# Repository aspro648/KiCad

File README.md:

# KiCad
My design files. Abandon all hope ye who enter here.

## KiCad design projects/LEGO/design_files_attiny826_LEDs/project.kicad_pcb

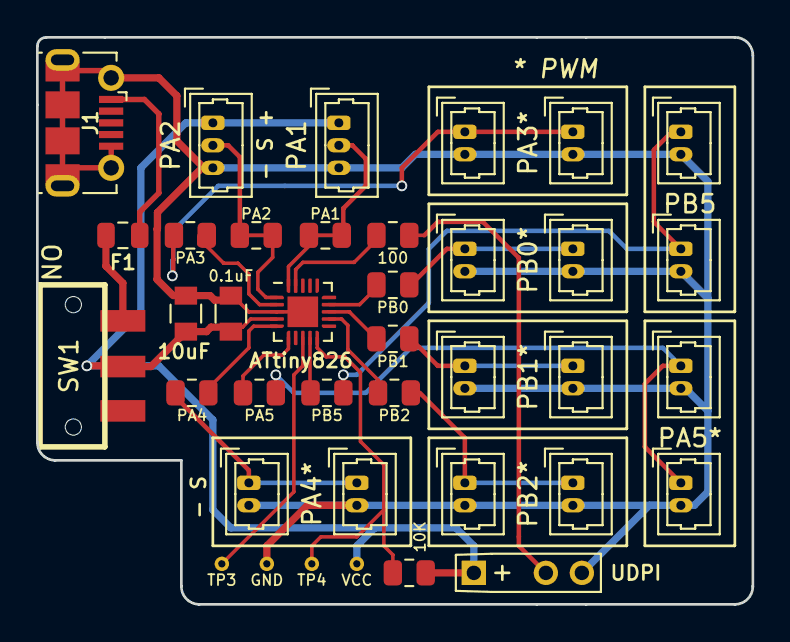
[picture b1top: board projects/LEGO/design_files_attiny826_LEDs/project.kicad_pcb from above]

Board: 2 copper layers, 39.8 x 31.5 mm, 38 parts (0 on the bottom side), 24 nets.

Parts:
C1: 10uF; C_0805
C2: 0.1uF; C_0805
F1: Polyfuse; Fuse_0805_2012Metric
J1: USB-MICRO; USB_Micro-B_Molex-105017-0001
J2, J10: PA4*; Molex_PicoBlade_53047-0210_1x02_P1.25mm_Vertical
J3: UDPI; UDPI_header
J4, J11: PA5*; Molex_PicoBlade_53047-0210_1x02_P1.25mm_Vertical
J5, J12: PB2*; Molex_PicoBlade_53047-0210_1x02_P1.25mm_Vertical
J6, J13: PB0*; Molex_PicoBlade_53047-0210_1x02_P1.25mm_Vertical
J7, J15: PB1*; Molex_PicoBlade_53047-0210_1x02_P1.25mm_Vertical
J8, J16: PA3*; Molex_PicoBlade_53047-0210_1x02_P1.25mm_Vertical
J9: PA2; Molex_PicoBlade_53047-0310_1x03_P1.25mm_Vertical
J14: PA1; Molex_PicoBlade_53047-0310_1x03_P1.25mm_Vertical
J17, J18: PB5; Molex_PicoBlade_53047-0210_1x02_P1.25mm_Vertical
JP1: PA2; J_0805
JP2: PA1; J_0805
R1: PA5; R_0805_2012Metric
R2: PB2; R_0805_2012Metric
R3: 100; R_0805_2012Metric
R4: PB0; R_0805_2012Metric
R5: PB1; R_0805_2012Metric
R6: PA4; R_0805_2012Metric
R7: PA3; R_0805_2012Metric
R8: PB5; R_0805_2012Metric
R9: 10K; R_0805_2012Metric
SW1: SW_SPST; SPST_SMD
TP1: GND; TestPoint
TP2: VCC; TestPoint
TP3: PA7; TestPoint
TP4: PB4; TestPoint
U1: ATtiny826; VQFN-20-1EP_3x3mm_P0.4mm_EP1.7x1.7mm

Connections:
/PIN_PA1: J14.2, JP2.1, JP2.2, U1.20
/PIN_PA2: J9.2, JP1.1, JP1.2, U1.1
/PIN_PA3: R7.1, U1.2
/PIN_PA4: R6.1, U1.5
/PIN_PA5: R1.1, U1.6
/PIN_PA7: TP3.1, U1.8
/PIN_PB0: R4.1, U1.14
/PIN_PB1: R5.1, U1.13
/PIN_PB2: R2.1, U1.12
/PIN_PB4: R9.2, TP4.1, U1.10
/PIN_PB5: R8.1, U1.9
/UPDI: R3.1, U1.19
GND: C1.2, C2.2, J1.5, J1.6, J2.2, J3.4, J4.2, J5.2, J6.2, J7.2, J8.2, J9.3, J10.2, J11.2, J12.2, J13.2, J14.3, J15.2, J16.2, J17.2, J18.2, TP1.1, U1.3, U1.21
unnamed: F1.2, J1.1
unnamed: J3.3, R3.2
unnamed: J2.1, J10.1, R6.2
unnamed: J4.1, J11.1, R1.2
unnamed: J5.1, J12.1, R2.2
unnamed: J6.1, J13.1, R4.2
unnamed: J7.1, J15.1, R5.2
unnamed: J8.1, J16.1, R7.2
unnamed: J17.1, J18.1, R8.2
VBUS: F1.1, SW1.1
VCC: C1.1, C2.1, J3.1, J9.1, J14.1, R9.1, SW1.2, TP2.1, U1.4

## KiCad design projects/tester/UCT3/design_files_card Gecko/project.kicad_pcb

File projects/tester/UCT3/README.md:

Universal Cable Tester V3

Bill Of Materials
----------------
  
- 1 ea., Perfect Purple PCB from OSH Park, with not so perfect layout from kicad.pcb file.
- 1 ea., U4 ATMEGA32U4-AU, IC MCU 8BIT 32KB FLASH 44TQFP, https://www.digikey.com/short/jb25pc
- 1 ea., Y1 CER RES 16.0000MHZ 15PF SMD, Murata CSTNE16M0V530000R0, https://www.digikey.com/short/8nzcmjh3
- 2 ea., C1 CAP CER 10UF 10V X5R 0805, Kemet C0805C106K8PAC7800, https://www.digikey.com/short/32v75tfv
- 23 ea., D1-D23 SMD LED GREEN 0603, Lite-On LTST-C191KGKT, https://www.digikey.com/short/ptwhtwz2
- 1 ea., F1 PTC RESET FUSE 6V 350MA 0805, Bell 0ZCK0035FF2G, https://www.digikey.com/short/b0qhczzp
- 2 ea., RV1, RV2 VARISTOR 10.8V 30A 0603, KYOCERA VCUG060050L1DP, https://www.digikey.com/short/0479hw0m
- 23 ea., R1-R23 Resistor 1K OHM SMD 0603, Stackpole RNCP0603FTD1K00, https://www.digikey.com/short/704h9hfn
- 2 ea., R24, R25 Resistor 22 OHM SMD 0603, Yageo RC0603JR-0722RL, https://www.digikey.com/short/93jrm3t2
- 1 ea., R26 Resistor 1M OHM SMD 0603 Yageo RC0603JR-071ML, https://www.digikey.com/short/z0jnrwbq
- 2 ea., SW1 SWITCH TACTILE SPST-NO 0.05A 12V, Wurth 434121025816, https://www.digikey.com/short/qbm0p0c9
- 1 ea., J1 CONN RCPT MICRO USB R/A SMD, Molex 1050170001, https://www.digikey.com/short/jb2205
- 2 ea., X1, X2 CONN EDGE DUAL FMALE 20POS, Samtek MEC8-110-02-L-D-RA1, https://www.digikey.com/short/f4rv8cjm
- 2 ea., ROUND STANDOFF M2.5 STEEL 2.7MM, Wurth 9774027151R, https://www.digikey.com/short/47zwt3m4
- 2 ea., M2.5x6 pan-head phillips screw
- 2 ea., Resistor 4K7 OHM SMD 0603

- 1 ea., 3535 RGB LED,  IN-PI33TBTPRPGPB https://www.digikey.com/short/qf2t8bqj

Card:
10K
24LC32AT-I/MC, https://www.digikey.com/short/r3f225vm
- 2 ea., M2.5 thumbscrew https://www.mcmaster.com/99607A263/
https://www.amazon.com/M2-5x6mm-Knurled-Screws-Stainless-Metric/dp/B01NBH813V

License
----------------
[Attribution-ShareAlike 3.0 United States (CC BY-SA 3.0 US)](https://creativecommons.org/licenses/by-sa/3.0/us/)

You are free to:

- Share — copy and redistribute the material in any medium or format
- Adapt — remix, transform, and build upon the material

Under the following terms:

- Attribution — You must give appropriate credit, provide a link to the license, and indicate if changes were made. You may do so in any reasonable manner, but not in any way that suggests the licensor endorses you or your use.
- ShareAlike — If you remix, transform, or build upon the material, you must distribute your contributions under the same license as the original.

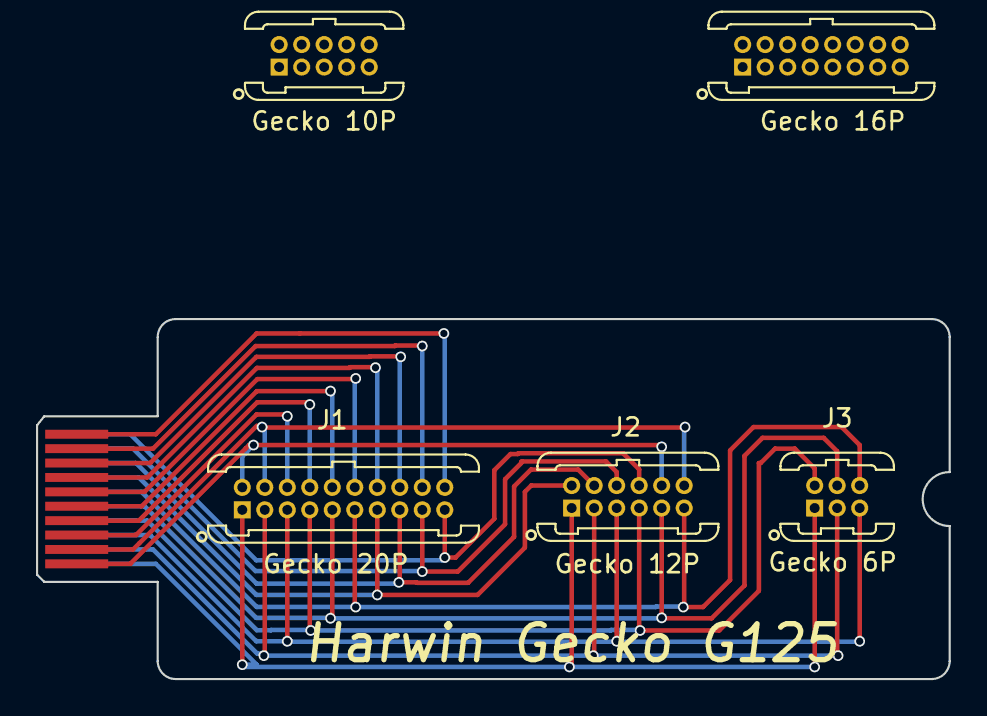
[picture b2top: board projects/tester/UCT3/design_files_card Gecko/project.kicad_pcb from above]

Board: 2 copper layers, 50.7 x 20.0 mm, 4 parts (0 on the bottom side), 20 nets.

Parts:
J0: Edge; MEC8_card
J1: Gecko 20P; Harwin_Gecko-G125-MVX2005L0X_2x10_P1.25mm_Vertical
J2: Gecko 12P; Harwin_Gecko-G125-MVX1205L0X_2x06_P1.25mm_Vertical
J3: Gecko 6P; Harwin_Gecko-G125-MVX0605L0X_2x03_P1.25mm_Vertical

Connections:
/01: J0.1, J1.1, J2.1, J3.1
/02: J0.2, J1.2, J2.2, J3.2
/03: J0.3, J1.3, J2.3, J3.3
/04: J0.4, J1.4, J2.4, J3.4
/05: J0.5, J1.5, J2.5, J3.5
/06: J0.6, J1.6, J2.6, J3.6
/07: J0.7, J1.7, J2.7
/08: J0.8, J1.8, J2.8
/09: J0.9, J1.9, J2.9
/10: J0.10, J1.10, J2.10
/11: J0.11, J1.11, J2.11
/12: J0.12, J1.12, J2.12
/13: J0.13, J1.13
/14: J0.14, J1.14
/15: J0.15, J1.15
/16: J0.16, J1.16
/17: J0.17, J1.17
/18: J0.18, J1.18
/19: J0.19, J1.19
/20: J0.20, J1.20

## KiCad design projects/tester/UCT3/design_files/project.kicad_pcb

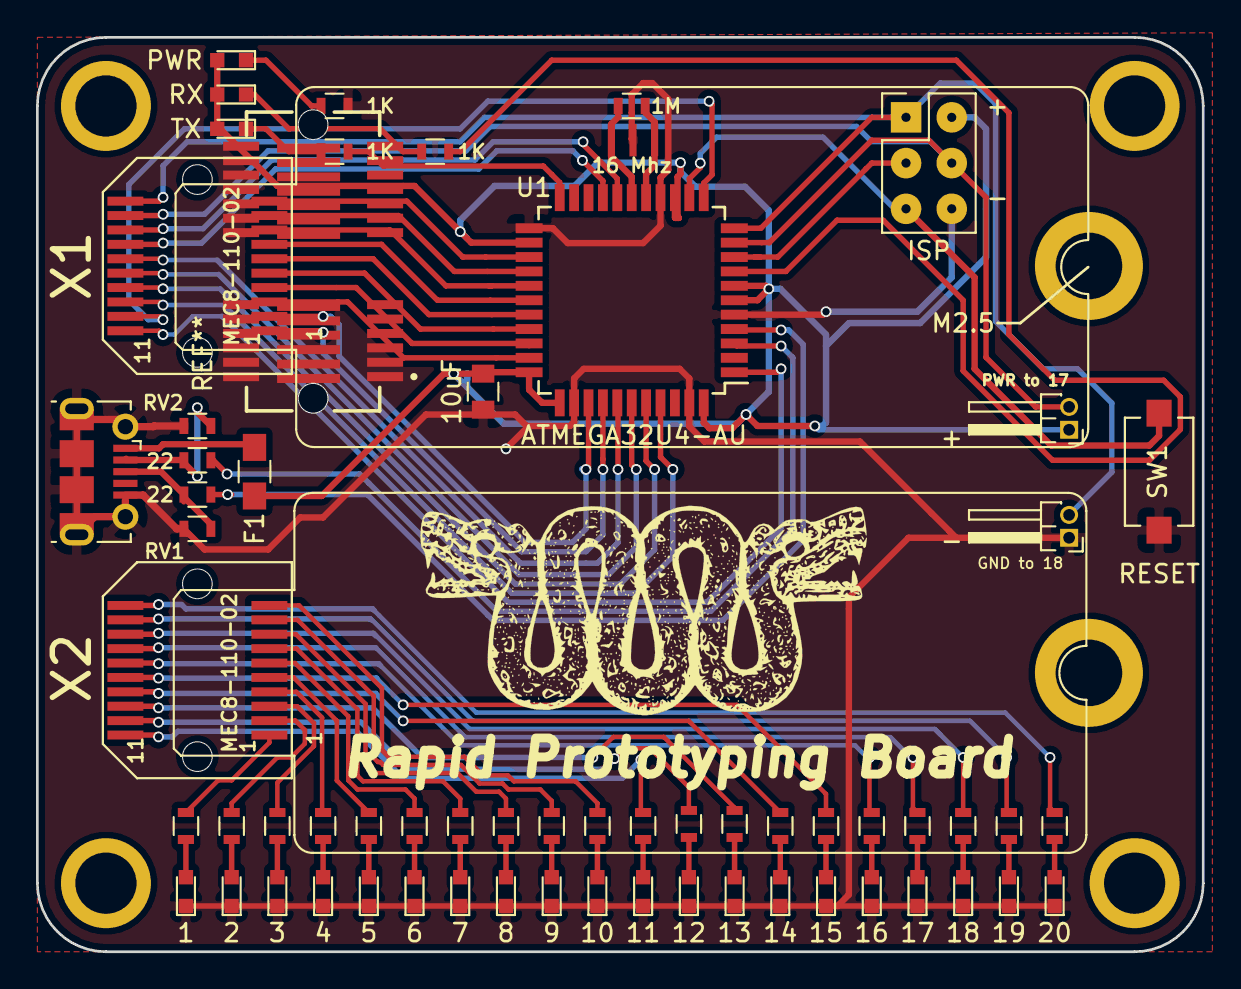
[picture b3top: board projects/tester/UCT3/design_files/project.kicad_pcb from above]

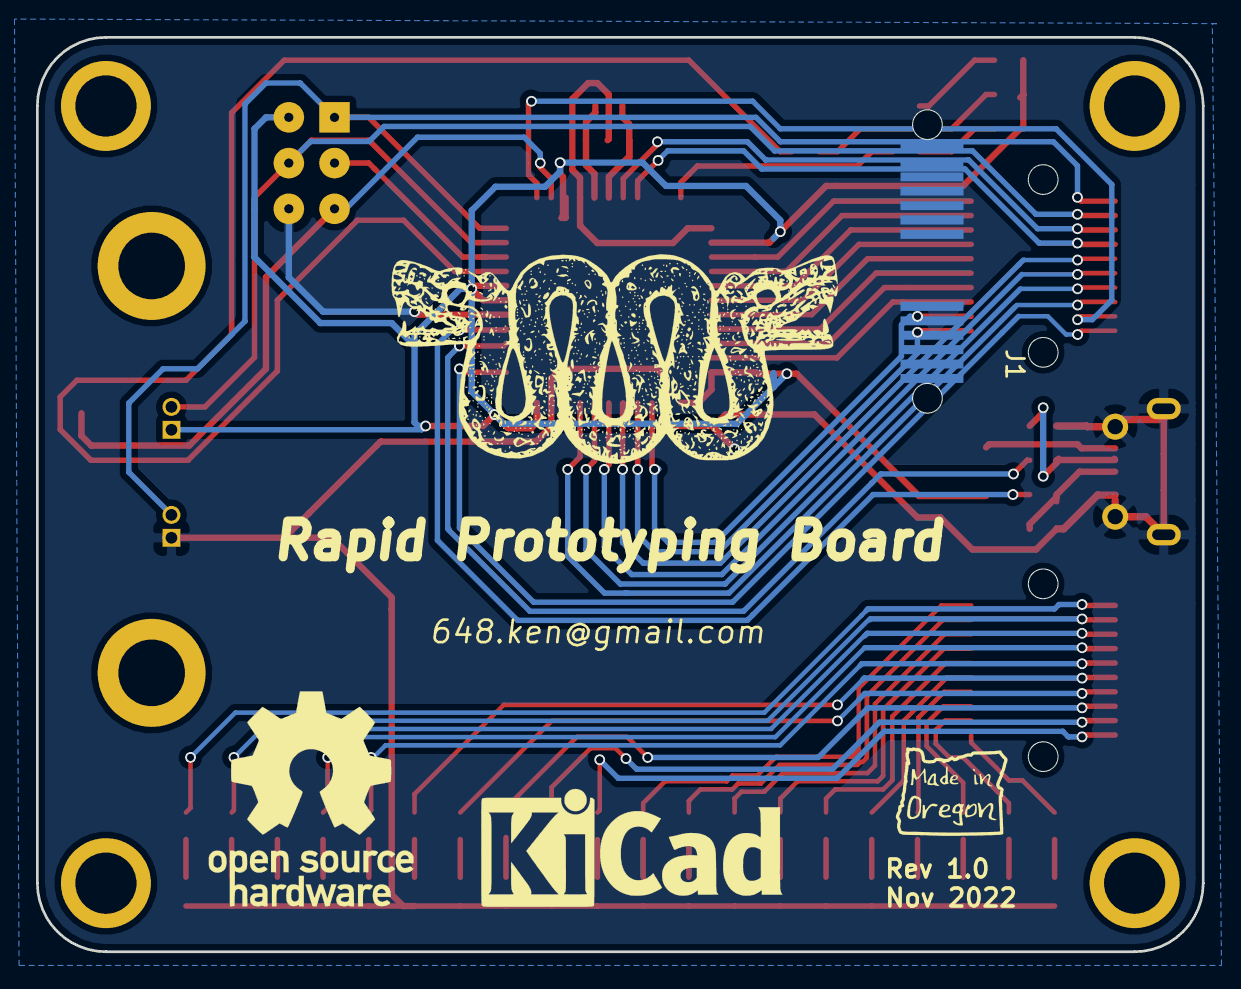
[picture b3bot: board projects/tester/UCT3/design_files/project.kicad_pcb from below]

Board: 2 copper layers, 64.8 x 50.8 mm, 76 parts (3 on the bottom side), 76 nets.

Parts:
C1: 10uF; C_0805
CardOutline1, CardOutline2: SYM_Arrow_Large; MEC8_card
D1: 1; LED_0603
D2: 2; LED_0603
D3: 3; LED_0603
D4: 4; LED_0603
D5: 5; LED_0603
D6: 6; LED_0603
D7: 7; LED_0603
D8: 8; LED_0603
D9: 9; LED_0603
D10: 10; LED_0603
D11: 11; LED_0603
D12: 12; LED_0603
D13: 13; LED_0603
D14: 14; LED_0603
D15: 15; LED_0603
D16: 16; LED_0603
D17: 17; LED_0603
D18: 18; LED_0603
D19: 19; LED_0603
D20: 20; LED_0603
D21: PWR; LED_0603
D22: TX; LED_0603
D23: RX; LED_0603
F1: Polyfuse; R_0805_HandSoldering
J1: Conn_02x13_Top_Bottom; MEC8-113-CARD
J1#2: USB_OTG; USB_Micro-B_Molex-105017-0001
J2: ISP; Pin_Header_Straight_2x03_Pitch2.54mm
JP1: PWR to 17; PinHeader_1x02_P1.27mm_Horizontal
JP2: GND to 18; PinHeader_1x02_P1.27mm_Horizontal
MadeInOregon1: SYM_Arrow_Large; MadeInOregonRev25
MadeWithKiCAD1: SYM_Arrow_Large; KiCad-Logo2_8mm_SilkScreen
OSHW1: SYM_Arrow_Large; OSHW-Logo_11.4x12mm_SilkScreen
P1, P2, P3, P4: M3; M3mount
P5, P6: Standoff; M25standoff
R1, R2, R3, R4, R5, R6, R7, R8, R9, R10, R11, R12, R13, R14, R15, R16, R17, R18, R19, R20, R21, R22, R23: 1K; R_0603
R24, R25: 22; R_0603
R26: 1M; R_0603
RV1, RV2: Varistor; R_0603
SW1: RESET; SW_TS10-63-26-BE-250-SMT-TR
SnakeBack1: SYM_Arrow_Large; Snake
SnakeFront1: SYM_Arrow_Large; Snake
U1: ATMEGA32U4-AU; TQFP-44_10x10mm_Pitch0.8mm
X1, X2: MEC8-110-02; MEC8_top_bottom
Y1: 16 Mhz; Resonator_SMD_CTSC_1.3mmx3.2mm

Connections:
+5V: C1.1, D21.2, D22.2, D23.2, F1.1, J2.2, JP1.1, U1.6, U1.7, U1.14, U1.24, U1.33, U1.34, U1.44
/A0: U1.36, X1.2
/A1: U1.37, X1.1
/A2: U1.38, X1.16
/A3: U1.39, X1.15
/A4: U1.40, X1.14
/A5: U1.41, X1.13
/D2_SDA: U1.19, X1.17
/D3_SCL: U1.18, X1.18
/D4: U1.25, X1.10
/D5: U1.31, X1.4
/D6: U1.27, X1.8
/D7: U1.1, X1.11
/D8: U1.28, X1.7
/D9: U1.29, X1.6
/D10: U1.30, X1.5
/D11: U1.12, X1.12
/D12: U1.26, X1.9
/D13: U1.32, X1.3
/D+: R24.1, U1.4
/D-: R25.1, U1.3
/MISO: J2.1, JP2.2, U1.11, X1.20
/MOSI: J2.4, JP1.2, U1.10, X1.19
/RXLED: R23.1, U1.8
/SCK: J2.3, U1.9
/TXLED: R22.1, U1.22
/~RESET: J2.5, SW1.2, U1.13
GND: C1.2, D1.1, D2.1, D3.1, D4.1, D5.1, D6.1, D7.1, D8.1, D9.1, D10.1, D11.1, D12.1, D13.1, D14.1, D15.1, D16.1, D17.1, D18.1, D19.1, D20.1, J1#2.5, J1#2.6, J2.6, JP2.1, R21.2, RV1.2, RV2.2, SW1.1, U1.5, U1.15, U1.23, U1.35, U1.43, Y1.2
unnamed: D1.2, R1.1
unnamed: D2.2, R2.1
unnamed: D3.2, R3.1
unnamed: D4.2, R4.1
unnamed: D5.2, R5.1
unnamed: D6.2, R6.1
unnamed: D7.2, R7.1
unnamed: D8.2, R8.1
unnamed: D9.2, R9.1
unnamed: D10.2, R10.1
unnamed: D11.2, R11.1
unnamed: D12.2, R12.1
unnamed: D13.2, R13.1
unnamed: D14.2, R14.1
unnamed: D15.2, R15.1
unnamed: D16.2, R16.1
unnamed: D17.2, R17.1
unnamed: D18.2, R18.1
unnamed: D19.2, R19.1
unnamed: D20.2, R20.1
unnamed: D21.1, R21.1
unnamed: D22.1, R22.2
unnamed: D23.1, R23.2
unnamed: F1.2, J1#2.1
unnamed: J1#2.2, R25.2, RV2.1
unnamed: J1#2.3, R24.2, RV1.1
unnamed: R1.2, X2.1
unnamed: R2.2, X2.2
unnamed: R3.2, X2.3
unnamed: R4.2, X2.4
unnamed: R5.2, X2.5
unnamed: R6.2, X2.6
unnamed: R7.2, X2.7
unnamed: R8.2, X2.8
unnamed: R9.2, X2.9
unnamed: R10.2, X2.10
unnamed: R11.2, X2.11
unnamed: R12.2, X2.12
unnamed: R13.2, X2.13
unnamed: R14.2, X2.14
unnamed: R15.2, X2.15
unnamed: R16.2, X2.16
unnamed: R17.2, X2.17
unnamed: R18.2, X2.18
unnamed: R19.2, X2.19
unnamed: R20.2, X2.20
unnamed: R26.1, U1.16, Y1.3
unnamed: R26.2, U1.17, Y1.1

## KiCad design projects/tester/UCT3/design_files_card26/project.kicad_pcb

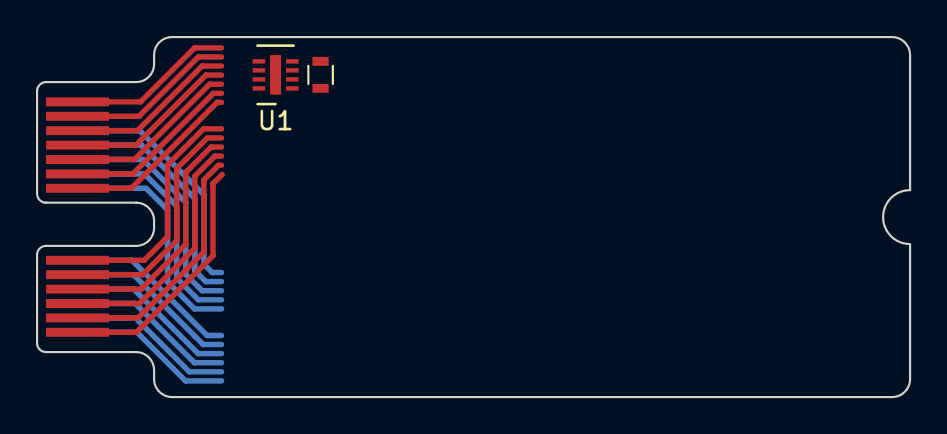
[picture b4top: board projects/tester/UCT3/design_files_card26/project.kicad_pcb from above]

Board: 2 copper layers, 48.5 x 20.0 mm, 3 parts (0 on the bottom side), 6 nets.

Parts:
R1: 10K; R_0603
U1: 24LC32; DFN-8-1EP_2x3mm_P0.5mm_EP0.61x2.2mm
X0: Card Edge; MEC8-113-CARD

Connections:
+5V: U1.8, X0.13
/A: R1.2, X0.12
/D2_SDA: U1.5, X0.25
/D3_SCL: U1.6, X0.24
GND: U1.2, U1.3, U1.4, X0.26
unnamed: R1.1, U1.1

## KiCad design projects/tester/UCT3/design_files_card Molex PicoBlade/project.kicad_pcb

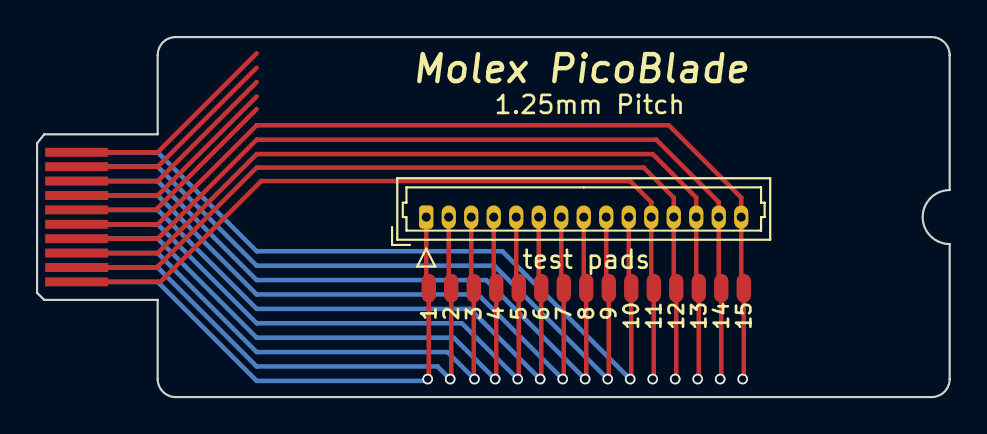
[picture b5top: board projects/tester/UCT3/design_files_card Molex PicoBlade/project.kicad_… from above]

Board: 2 copper layers, 50.7 x 20.0 mm, 3 parts (0 on the bottom side), 15 nets.

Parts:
J0: Card Edge; MEC8_card
J1: 1.25mm Pitch; Molex_PicoBlade_53047-1510_1x15_P1.25mm_Vertical
J3: test pads; Molex_PicoBlade_53261-1571_1x15-1MP_P1.25mm_Horizontal

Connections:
/01: J0.1, J1.1, J3.1
/02: J0.2, J1.2, J3.2
/03: J0.3, J1.3, J3.3
/04: J0.4, J1.4, J3.4
/05: J0.5, J1.5, J3.5
/06: J0.6, J1.6, J3.6
/07: J0.7, J1.7, J3.7
/08: J0.8, J1.8, J3.8
/09: J0.9, J1.9, J3.9
/10: J0.10, J1.10, J3.10
/11: J0.11, J1.11, J3.11
/12: J0.12, J1.12, J3.12
/13: J0.13, J1.13, J3.13
/14: J0.14, J1.14, J3.14
/15: J0.15, J1.15, J3.15

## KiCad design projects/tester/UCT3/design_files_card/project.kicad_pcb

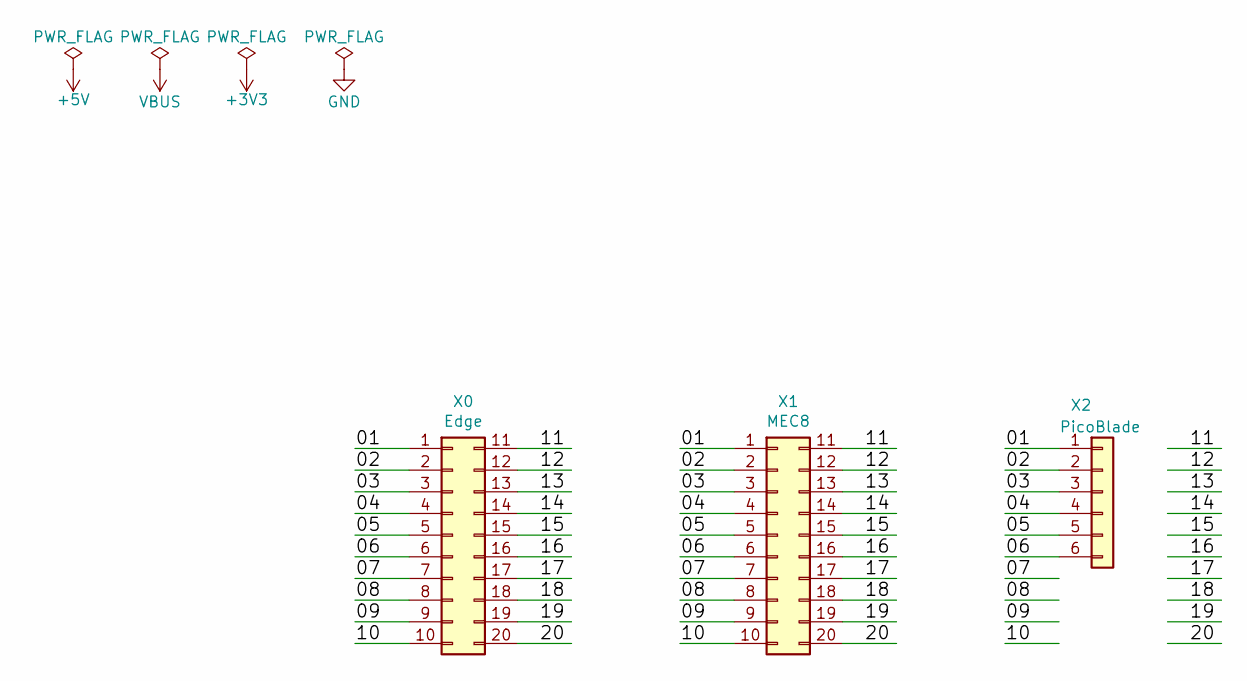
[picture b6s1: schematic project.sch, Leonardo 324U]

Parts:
X0: Edge; MEC8_card
X1: MEC8; MEC8_top_bottom
X2: PicoBlade; Molex_PicoBlade_53047-0610_1x06_P1.25mm_Vertical

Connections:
/01: X0.1, X1.1, X2.1
/02: X0.2, X1.2, X2.2
/03: X0.3, X1.3, X2.3
/04: X0.4, X1.4, X2.4
/05: X0.5, X1.5, X2.5
/06: X0.6, X1.6, X2.6
/07: X0.7, X1.7
/08: X0.8, X1.8
/09: X0.9, X1.9
/10: X0.10, X1.10
/11: X0.11, X1.11
/12: X0.12, X1.12
/13: X0.13, X1.13
/14: X0.14, X1.14
/15: X0.15, X1.15
/16: X0.16, X1.16
/17: X0.17, X1.17
/18: X0.18, X1.18
/19: X0.19, X1.19
/20: X0.20, X1.20

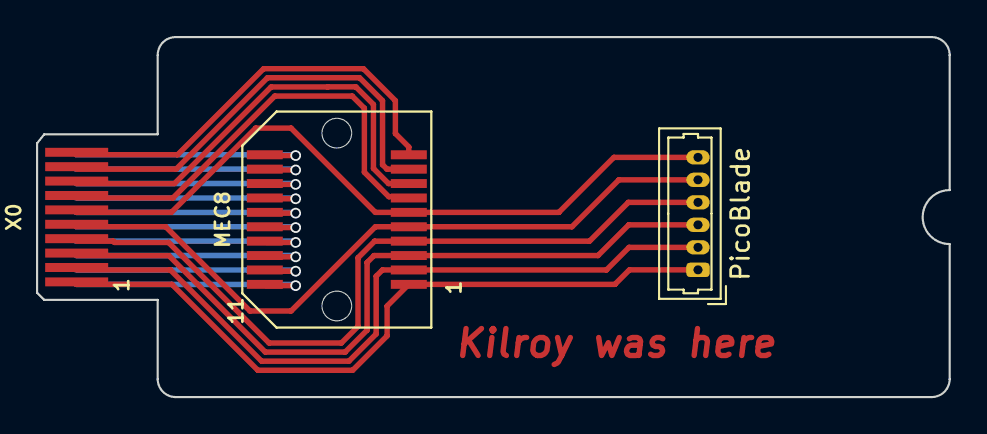
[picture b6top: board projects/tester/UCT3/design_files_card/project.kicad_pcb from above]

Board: 2 copper layers, 50.7 x 20.0 mm, 3 parts (0 on the bottom side), 20 nets.

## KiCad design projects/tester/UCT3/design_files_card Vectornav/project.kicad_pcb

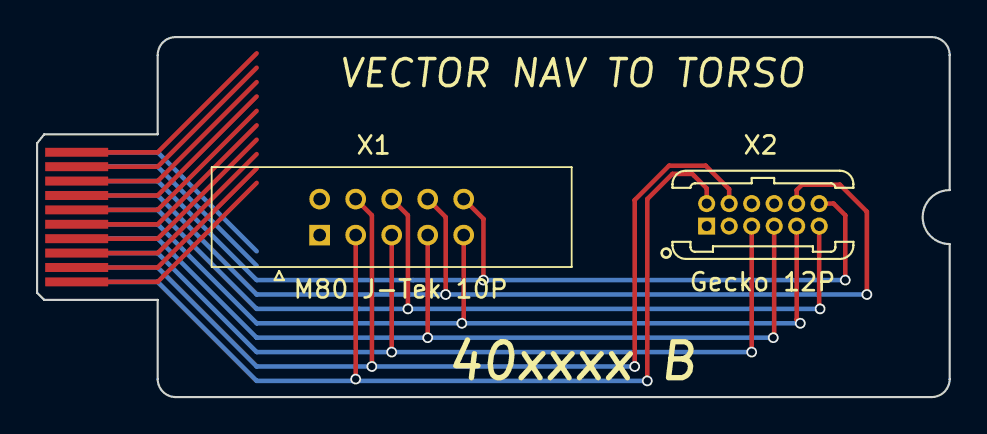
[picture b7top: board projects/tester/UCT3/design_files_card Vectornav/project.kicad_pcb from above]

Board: 2 copper layers, 50.7 x 20.0 mm, 3 parts (0 on the bottom side), 8 nets.

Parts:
J0: Edge; MEC8_card
X1: M80 J-Tek 10P; M80-5T110YYMC
X2: Gecko 12P; Harwin_Gecko-G125-MVX1205L0X_2x06_P1.25mm_Vertical

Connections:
/01: J0.1, X1.2, X2.7
/02: J0.2, X1.7, X2.8
/03: J0.3, X1.3, X2.3
/04: J0.4, X1.4, X2.4
/05: J0.5, X1.5, X2.5
/06: J0.6, X1.8, X2.6
/07: J0.7, X1.9, X2.11
/08: J0.8, X1.10, X2.12

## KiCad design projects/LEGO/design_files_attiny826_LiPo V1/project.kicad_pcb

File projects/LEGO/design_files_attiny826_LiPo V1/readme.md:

Attiny826 Lego LiPo Badge

Bill Of Materials
----------------

- 1 ea., Perfect Purple PCB from OSH Park from [design_files/project.kicad_pcb](project.kicad_pcb) file.
- 1 ea., Attiny826 IC MCU 8BIT 8KB FLASH 20VQFN, https://www.digikey.com/short/b9cq02np
- 3 ea., CAP CER 10uF 50V 0805,
- 1 ea., CAP CER 0.1uF 0605
- 1 ea., 3.7V LiPo (VERIFY CONNECTOR AND POLARITY).
- 1 ea., CONN RCPT MICRO USB R/A SMD, Molex 1050170001, https://www.digikey.com/short/jb2205
- 1 ea., PTC RESET FUSE 15V 100MA 0805, Bel Fuse 0ZCK0010FF2G, https://www.digikey.com/short/v24142q9
- 1 ea., JST SH CONN HEADER SMD R/A 2POS 1MM, SM02B-SRSS-TB(LF)(SN), https://www.digikey.com/short/z4vw0z
- 1 ea., CONN HOUSING SH 2POS 1MM WHITE, SHR-02V-S-B, https://www.digikey.com/short/0b2m0rpt
- 8 ea., RES SMD 100 OHM 5% 1/8W 0603
- 2 ea., RES SMD 1K OHM, 0603
- 3 ea., RES SMD 10K OHM, 0603
- 1 ea., RES SMD 39K OHM, 0603
- 1 ea., SMD SPST switch, C&K JS102011SCQN, https://www.digikey.com/short/5m7mwm1b

- LEDs: 
    - 3 ea., LED RED DIFFUSED 0603 SMD (CHG)
	- 1 ea., LED GREEN DIFFUSE 0603 SMD (DONE)
    - 7 ea., LED WHITE 0805, https://www.digikey.com/short/j45hzdv8

Revisions
----------------
- Revision 0.1 - Pin numbering to Konde recommended.  Divider Vcc to PIN_PC0.  JST SH header.

License
----------------
[Attribution-ShareAlike 3.0 United States (CC BY-SA 3.0 US)](https://creativecommons.org/licenses/by-sa/3.0/us/)

You are free to:

- Share — copy and redistribute the material in any medium or format
- Adapt — remix, transform, and build upon the material

Under the following terms:

- Attribution — You must give appropriate credit, provide a link to the license, and indicate if changes were made. You may do so in any reasonable manner, but not in any way that suggests the licensor endorses you or your use.
- ShareAlike — If you remix, transform, or build upon the material, you must distribute your contributions under the same license as the original.

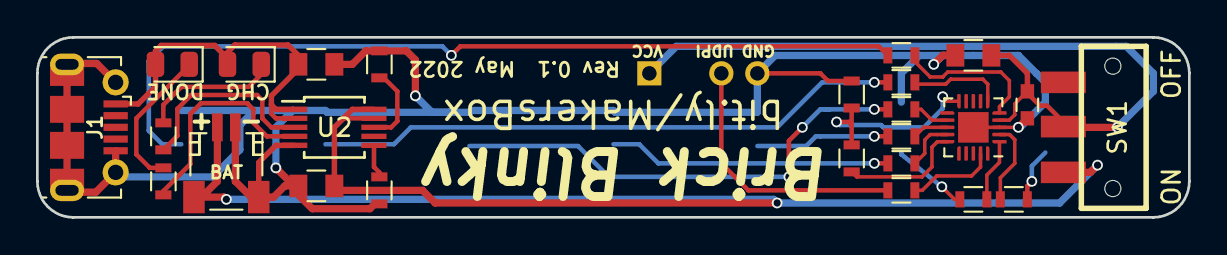
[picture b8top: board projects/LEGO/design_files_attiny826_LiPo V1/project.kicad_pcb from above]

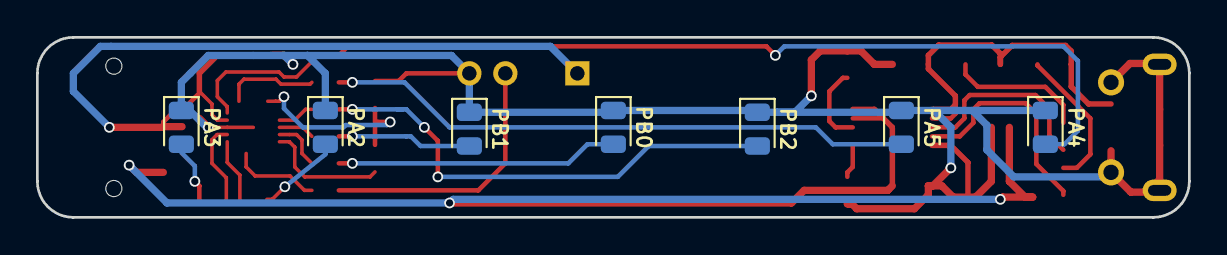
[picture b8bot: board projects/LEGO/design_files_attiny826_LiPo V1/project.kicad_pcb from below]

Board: 2 copper layers, 64.0 x 10.0 mm, 33 parts (8 on the bottom side), 28 nets.

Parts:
C1, C3, C4: 10uF; C_0805
C2: 0.1uF; C_0603
D1: CHG; LED_0805_2012Metric
D2: DONE; LED_0805_2012Metric
D3: PA4; LED_0805_2012Metric
D4: PA5; LED_0805_2012Metric
D5: PB1; LED_0805_2012Metric
D6: PB2; LED_0805_2012Metric
D7: PB0; LED_0805_2012Metric
D8: PA3; LED_0805_2012Metric
D9: PA2; LED_0805_2012Metric
J1: USB-MICRO; USB_Micro-B_Molex-105017-0001
J2: BAT; JST_SH_SM02B-SRSS-TB_02x1.00mm_Angled
J3: UDPI; UDPI_header
R1: 39K; R_0603
R2, R13, R14: 10K; R_0603
R3, R6, R7, R8, R9, R10, R11, R12: 100; R_0603
R4, R5: 1K; R_0603
SW1: SW_SPST; SPST_SMD
U1: ATtiny826; VQFN-20-1EP_3x3mm_P0.4mm_EP1.7x1.7mm
U2: MCP73833; MSOP-10_3x3mm_Pitch0.5mm

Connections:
+BATT: C4.1, J2.1, SW1.1, U2.9, U2.10
/PIN_PA2: R11.1, U1.1
/PIN_PA3: R12.1, U1.2
/PIN_PA4: R6.1, U1.5
/PIN_PA5: R7.1, U1.6
/PIN_PB0: R10.1, U1.14
/PIN_PB1: R8.1, U1.13
/PIN_PB2: R9.1, U1.12
/PIN_PB4: R1.2, R2.1, U1.10
/PIN_PC0: R1.1, U1.15
/UPDI: R3.1, U1.19
GND: C1.2, C2.2, C3.2, C4.2, D3.1, D4.1, D5.1, D6.1, D7.1, D8.1, D9.1, J1.5, J1.6, J2.2, J3.4, R2.2, R13.2, R14.2, U1.3, U1.21, U2.5
unnamed: D1.1, R4.2
unnamed: D2.1, R5.2
unnamed: D3.2, R6.2
unnamed: D4.2, R7.2
unnamed: D5.2, R8.2
unnamed: D6.2, R9.2
unnamed: D7.2, R10.2
unnamed: D8.2, R12.2
unnamed: D9.2, R11.2
unnamed: J3.3, R3.2
unnamed: R4.1, U2.3
unnamed: R5.1, U2.4
unnamed: R13.1, U2.6
unnamed: R14.1, U2.8
VBUS: C3.1, D1.2, D2.2, J1.1, U2.1, U2.2
VCC: C1.1, C2.1, J3.1, SW1.2, U1.4

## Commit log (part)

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2018-03-30 Rename chirp to rroll. Rev 0.3
2018-03-30 Updating markdown.
2018-03-30 rroll to fab
2018-04-21 OSH Park I Can Solder to manufacture
2018-04-26 TARDIS to fab
2018-05-07 Updated to include licence and BOM.
2018-05-16 Pogo V0.1
2018-05-16 update schematic
2018-05-17 Tardis firmware.
2018-05-17 LED Eyes
2018-07-22 Update from work laptop
2018-07-23 cleanup
2018-08-17 Toorcon release to fab
2018-08-23 Beetje LiPo to production
2018-08-27 Yoda
2018-09-08 Upates
2018-10-11 upsRWA
2018-10-29 updatess
2018-11-09 Udates
2018-12-15 Firmware update
2019-03-05 Rename
2019-04-18 Updtaes
2019-06-06 Iupdates
2019-09-23 Updaate
2020-02-17 Taris silk screen update
2020-02-26 Updz
2020-02-27 SMD Challenge PDFs
2021-02-09 Updates, Freecad
2021-02-10 updaters
2021-03-31 updates :
2021-10-30 updats
2022-05-03 Updaes
2022-05-10 to the FAB!
